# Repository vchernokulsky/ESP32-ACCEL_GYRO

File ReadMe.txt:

Структура проекта:

hardware - проект разработанного устройства для САПР KiCad

firmware - исходники прошивки для устройства (Micropython)

software - исходники приложения для сбора данных (Microsoft Visual Studio 2019 / C# WPF)

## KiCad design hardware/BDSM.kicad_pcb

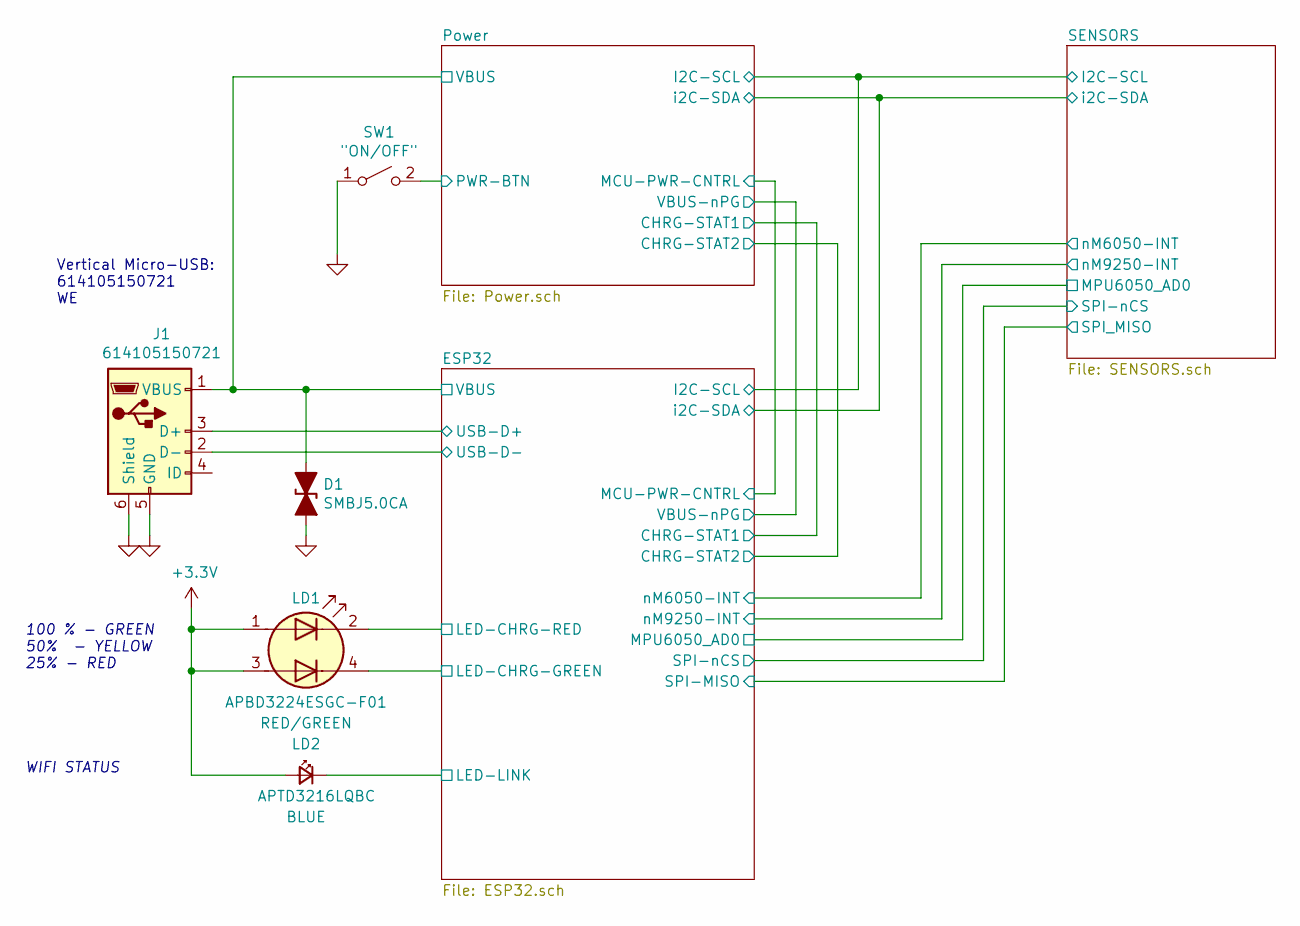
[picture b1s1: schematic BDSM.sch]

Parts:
D1: SMBJ5.0CA; D_SMB; PartNumber SMBJ5.0CA
J1: 614105150721; USB_Micro-B_Wuerth_614105150721_Vertical; PartNumber 614105150721
LD1: RED/GREEN; LED_Kingbright_APBD3224ESGC; PartNumber APBD3224ESGC-F01
LD2: BLUE; LED_1206_3216Metric_Pad1.42x1.75mm_HandSolder; PartNumber APTD3216LQBC
SW1: \"ON/OFF\"; Switch_Tactile_SMD_6x6mm; PartNumber 5-1437565-0

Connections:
+3V3: LD1.1 (A1), LD1.3 (A2), LD2.2 (A); also elsewhere on the board
/ESP32/LED-CHRG-GREEN: LD1.4 (K2); also elsewhere on the board
/ESP32/LED-CHRG-RED: LD1.2 (K1); also elsewhere on the board
/ESP32/LED-LINK: LD2.1 (K); also elsewhere on the board
/ESP32/USB-D+: J1.3 (D+); also elsewhere on the board
/ESP32/USB-D-: J1.2 (D-); also elsewhere on the board
/ESP32/VBUS: D1.1 (A1), J1.1 (VBUS); also elsewhere on the board
/Power/PWR-BTN: SW1.2 (B); also elsewhere on the board
GNDA: D1.2 (A2), J1.5 (GND), J1.6 (Shield), SW1.1 (A); also elsewhere on the board

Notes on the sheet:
Vertical Micro-USB: 614105150721 WE
100 % - GREEN 50% - YELLOW 25% - RED
WIFI STATUS

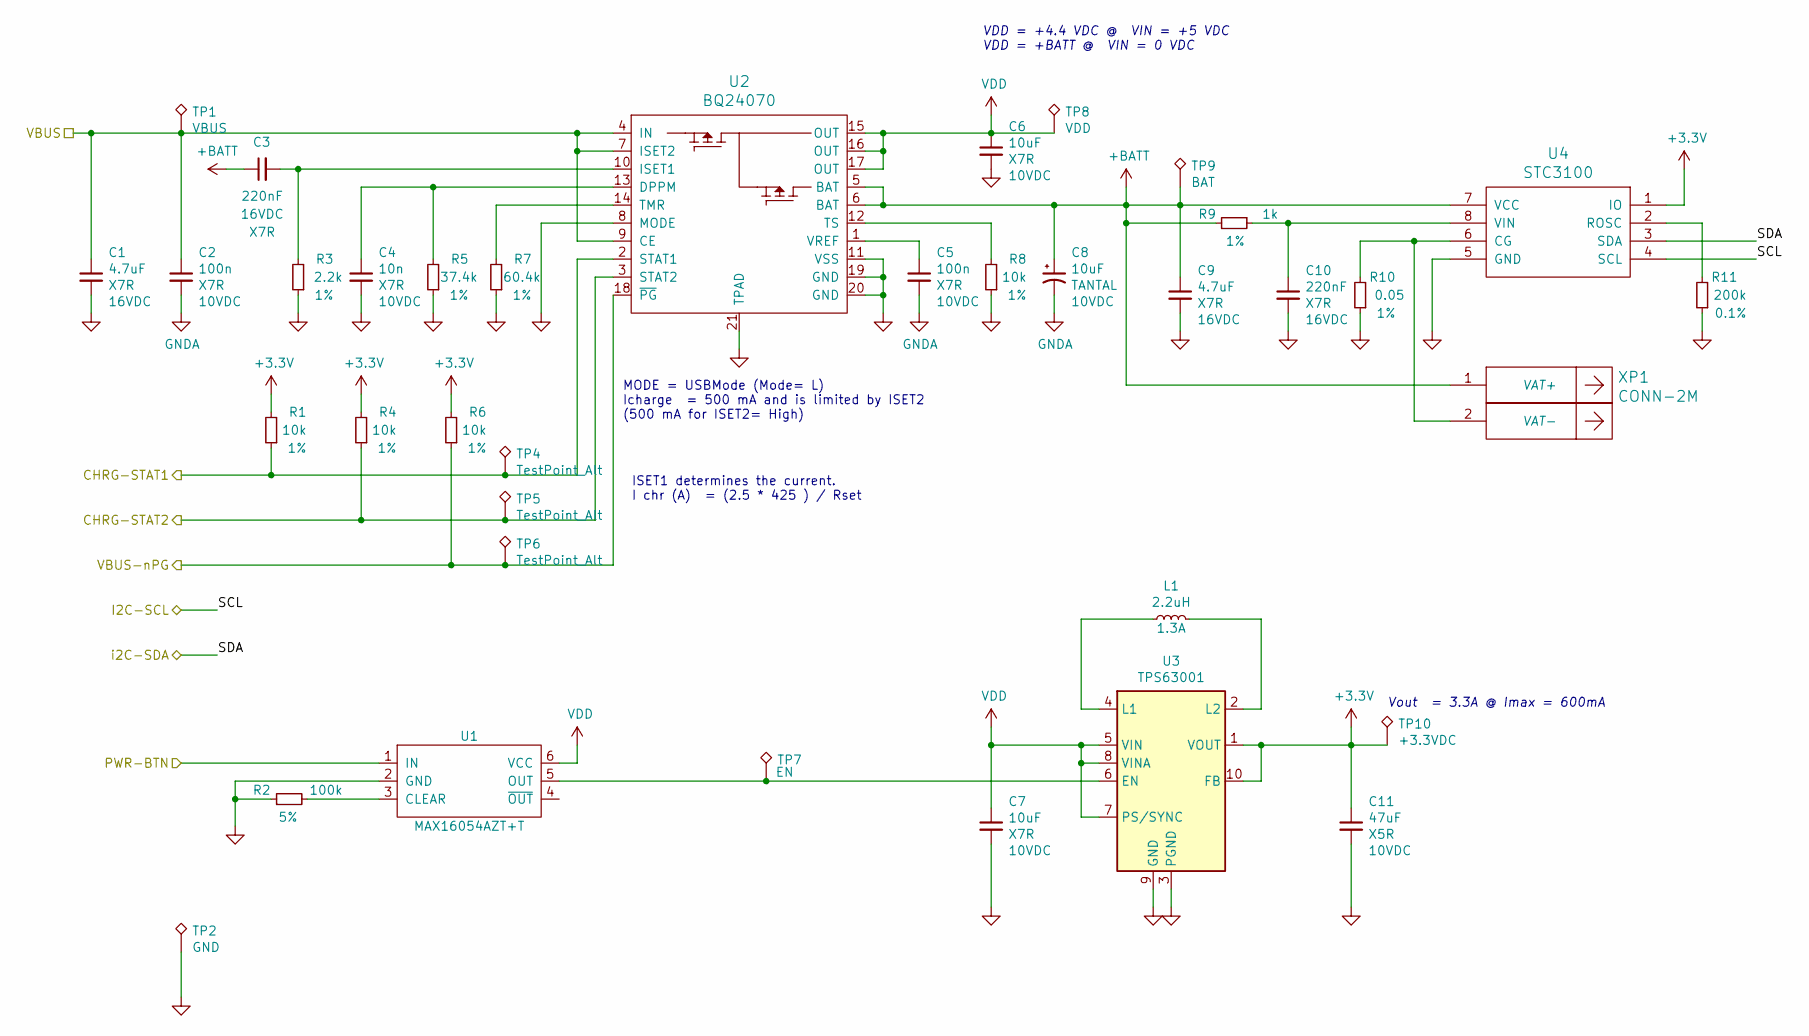
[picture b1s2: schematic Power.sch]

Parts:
C1, C9: 4.7uF; C_0805_2012Metric; Tolerance X7R; PartNumber CC0805KKX7R7BB105
C2, C5: 100n; C_0603_1608Metric; Tolerance X7R; PartNumber CC0603KRX7R9BB104
C3, C10: 220nF; C_0603_1608Metric; Tolerance X7R; PartNumber CC0603KRX7R7BB224
C4: 10n; C_0603_1608Metric; Tolerance X7R; PartNumber CC0603KRX7R9BB103
C6, C7: 10uF; C_0805_2012Metric; Tolerance X7R; PartNumber CL21B106KOQNNNE
C8: 10uF; CP_EIA-3528-21_Kemet-B; Tolerance TANTAL; PartNumber TAJB106K010RNJ
C11: 47uF; C_1206_3216Metric; Tolerance X5R; PartNumber C3216X5R1C476M160AB
L1: 2.2uH; L_1008_2520Metric; PartNumber LQM2HPN2R2MG0L
R1, R4, R6, R8: 10k; R_0603_1608Metric; Tolerance 1%; PartNumber RC0603FR-0710KL
R2: 100k; R_0603_1608Metric; Tolerance 5%; PartNumber RC0603JR-07100KL
R3: 2.2k; R_0603_1608Metric; Tolerance 1%; PartNumber RC0603FR-072K2L
R5: 37.4k; R_0603_1608Metric; Tolerance 1%; PartNumber RC0603FR-0737K4L
R7: 60.4k; R_0603_1608Metric; Tolerance 1%; PartNumber RC0603FR-0760K4L
R9: 1k; R_0603_1608Metric; Tolerance 1%; PartNumber CRCW06031K00FKEA
R10: 0.05; R_1206_3216Metric; Tolerance 1%; PartNumber RL1206FR-070R05L
R11: 200k; R_0603_1608Metric; Tolerance 0.1%; PartNumber RC0603FR-07200KL
TP1: VBUS; TestPoint_Pad_1.0x1.0mm; PartNumber PCB
TP2: GND; TestPoint_Keystone_5019_Minature; PartNumber PCB
TP4, TP5, TP6: TestPoint_Alt; TestPoint_Pad_1.0x1.0mm; PartNumber PCB
TP7: EN; TestPoint_Pad_1.0x1.0mm; PartNumber PCB
TP8: VDD; TestPoint_Pad_1.0x1.0mm; PartNumber PCB
TP9: BAT; TestPoint_Pad_1.0x1.0mm; PartNumber PCB
TP10: +3.3VDC; TestPoint_Pad_1.0x1.0mm; PartNumber PCB
U1: MAX16054AZT+T; SOT-23-6; PartNumber MAX16054AZT+T
U2: BQ24070; Texas_VQFN-RHL-20_ThermalVias; PartNumber BQ24070RHLR
U3: TPS63001; Texas_DRC0010J_ThermalVias; PartNumber TPS63001DRCT
U4: STC3100; MSOP-8_3x3mm_P0.65mm; PartNumber STC3100IST
XP1: CONN-2M; CWF-2R; PartNumber CWF-2R

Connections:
+3V3: C11.1, R1.2, R4.2, R6.2, TP10.1, U3.1 (VOUT), U3.10 (FB), U4.1 (IO); also elsewhere on the board
+BATT: C3.1, C8.1, C9.1, R9.2, TP9.1, U2.5 (BAT), U2.6 (BAT), U4.7 (VCC), XP1.1
/ESP32/CHRG-STAT1: R1.1, TP4.1, U2.2 (STAT1); also elsewhere on the board
/ESP32/CHRG-STAT2: R4.1, TP5.1, U2.3 (STAT2); also elsewhere on the board
/ESP32/I2C-SCL: U4.4 (SCL); also elsewhere on the board
/ESP32/VBUS: C1.1, C2.1, TP1.1, U2.4 (IN), U2.7 (ISET2), U2.9 (CE); also elsewhere on the board
/ESP32/VBUS-nPG: R6.1, TP6.1, U2.18 (~PG); also elsewhere on the board
/ESP32/i2C-SDA: U4.3 (SDA); also elsewhere on the board
/Power/PWR-BTN: U1.1 (IN); also elsewhere on the board
GNDA: C1.2, C2.2, C4.2, C5.2, C6.2, C7.2, C8.2, C9.2, C10.2, C11.2, R2.1, R3.1, R5.1, R7.1, R8.1, R10.1, R11.1, TP2.1, U1.2 (GND), U2.8 (MODE), U2.11 (VSS), U2.19 (GND), U2.20 (GND), U2.21 (TPAD), U3.3 (PGND), U3.9 (GND), U3.11 (PGND), U4.5 (GND); also elsewhere on the board
unnamed: C3.2, R3.2, U2.10 (ISET1)
unnamed: C4.1, R5.2, U2.13 (DPPM)
unnamed: C5.1, U2.1 (VREF)
unnamed: C10.1, R9.1, U4.8 (VIN)
unnamed: L1.1, U3.4 (L1)
unnamed: L1.2, U3.2 (L2)
unnamed: R2.2, U1.3 (CLEAR)
unnamed: R7.2, U2.14 (TMR)
unnamed: R8.2, U2.12 (TS)
unnamed: R10.2, U4.6 (CG), XP1.2
unnamed: R11.2, U4.2 (ROSC)
unnamed: TP7.1, U1.5 (OUT), U3.6 (EN)
VDD: C6.1, C7.1, TP8.1, U1.6 (VCC), U2.15 (OUT), U2.16 (OUT), U2.17 (OUT), U3.5 (VIN), U3.7 (PS/SYNC), U3.8 (VINA)

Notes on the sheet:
VDD = +4.4 VDC @ VIN = +5 VDC VDD = +BATT @ VIN = 0 VDC
ISET1 determines the current. I chr (A) = (2.5 * 425 ) / Rset
MODE = USBMode (Mode= L) Icharge = 500 mA and is limited by ISET2 (500 mA for ISET2= High)
Vout = 3.3A @ Imax = 600mA

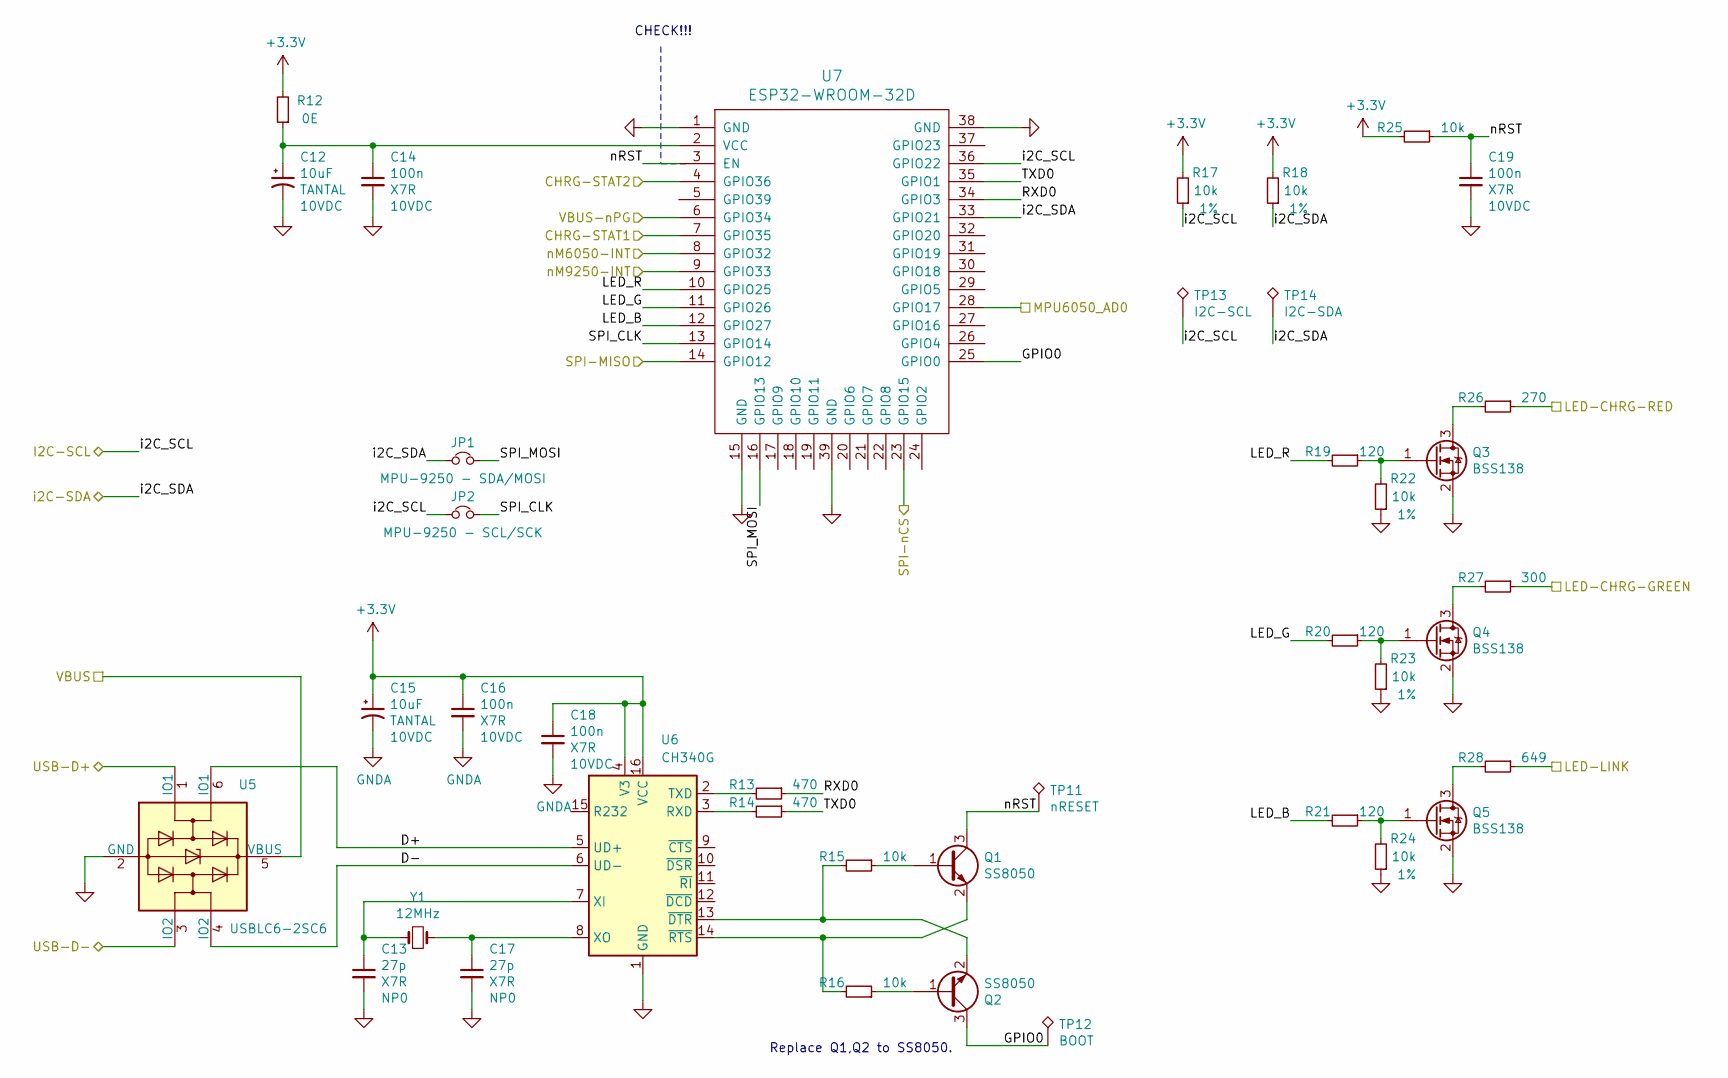
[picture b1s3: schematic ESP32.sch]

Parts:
C12, C15: 10uF; CP_EIA-3528-21_Kemet-B; Tolerance TANTAL; PartNumber TAJB106K010RNJ
C13, C17: 27p; C_0603_1608Metric; Tolerance X7R; PartNumber CC0603JRNPO9BN270
C14, C16, C18, C19: 100n; C_0603_1608Metric; Tolerance X7R; PartNumber CC0603KRX7R9BB104
JP1: MPU-9250 - SDA/MOSI; SolderJumper-2_P1.3mm_Open_TrianglePad1.0x1.5mm; PartNumber PCB
JP2: MPU-9250 - SCL/SCK; SolderJumper-2_P1.3mm_Open_TrianglePad1.0x1.5mm; PartNumber PCB
Q1, Q2: SS8050; SOT-23; PartNumber SS8050
Q3, Q4, Q5: BSS138; SOT-23; PartNumber BSS138LT1G
R12: 0E; R_0603_1608Metric; PartNumber RC0603FR-070RL
R13, R14: 470; R_0603_1608Metric; PartNumber RC0603FR-07470RL
R15, R16, R25: 10k; R_0603_1608Metric; PartNumber RC0603FR-0710KL
R17, R18, R22, R23, R24: 10k; R_0603_1608Metric; Tolerance 1%; PartNumber RC0603FR-0710KL
R19, R20, R21: 120; R_0603_1608Metric; PartNumber RC0603FR-07120RL
R26: 270; R_0603_1608Metric; PartNumber RC0603FR-07270RL
R27: 300; R_0603_1608Metric; PartNumber RC0603FR-07300RL
R28: 649; R_0603_1608Metric; PartNumber RC0603FR-07649RL
TP11: nRESET; TestPoint_Pad_1.0x1.0mm; PartNumber PCB
TP12: BOOT; TestPoint_Pad_1.0x1.0mm; PartNumber PCB
TP13: I2C-SCL; TestPoint_Pad_2.0x2.0mm; PartNumber PCB
TP14: I2C-SDA; TestPoint_Pad_2.0x2.0mm; PartNumber PCB
U5: USBLC6-2SC6; SOT-23-6; PartNumber USBLC6-2SC6
U6: CH340G; SOIC-16_3.9x9.9mm_P1.27mm; PartNumber CH340G
U7: ESP32-WROOM-32D; PartNumber ESP32-WROOM-32D
Y1: 12MHz; ABM3; PartNumber ABM3-12.000MHZ-D2Y-T

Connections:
+3V3: C15.1, C16.1, C18.1, R12.2, R17.2, R18.2, R25.2, U6.4 (V3), U6.16 (VCC); also elsewhere on the board
/ESP32/CHRG-STAT1: U7.7 (GPIO35); also elsewhere on the board
/ESP32/CHRG-STAT2: U7.4 (GPIO36); also elsewhere on the board
/ESP32/D+: U5.6 (IO1), U6.5 (UD+)
/ESP32/D-: U5.4 (IO2), U6.6 (UD-)
/ESP32/GPIO0: Q2.3 (C), TP12.1, U7.25 (GPIO0)
/ESP32/I2C-SCL: JP2.1, R17.1, TP13.1, U7.36 (GPIO22); also elsewhere on the board
/ESP32/LED-CHRG-GREEN: R27.1; also elsewhere on the board
/ESP32/LED-CHRG-RED: R26.1; also elsewhere on the board
/ESP32/LED-LINK: R28.1; also elsewhere on the board
/ESP32/LED_B: R21.2, U7.12 (GPIO27)
/ESP32/LED_G: R20.2, U7.11 (GPIO26)
/ESP32/LED_R: R19.2, U7.10 (GPIO25)
/ESP32/MPU6050_AD0: U7.28 (GPIO17); also elsewhere on the board
/ESP32/RXD0: R13.1, U7.34 (GPIO3)
/ESP32/SPI-MISO: U7.14 (GPIO12); also elsewhere on the board
/ESP32/SPI-nCS: U7.23 (GPIO15); also elsewhere on the board
/ESP32/SPI_CLK: JP2.2, U7.13 (GPIO14)
/ESP32/SPI_MOSI: JP1.2, U7.16 (GPIO13)
/ESP32/TXD0: R14.1, U7.35 (GPIO1)
/ESP32/USB-D+: U5.1 (IO1); also elsewhere on the board
/ESP32/USB-D-: U5.3 (IO2); also elsewhere on the board
/ESP32/VBUS: U5.5 (VBUS); also elsewhere on the board
/ESP32/VBUS-nPG: U7.6 (GPIO34); also elsewhere on the board
/ESP32/i2C-SDA: JP1.1, R18.1, TP14.1, U7.33 (GPIO21); also elsewhere on the board
/ESP32/nM6050-INT: U7.8 (GPIO32); also elsewhere on the board
/ESP32/nM9250-INT: U7.9 (GPIO33); also elsewhere on the board
/ESP32/nRST: C19.1, Q1.3 (C), R25.1, TP11.1, U7.3 (EN)
GNDA: C12.2, C13.2, C14.2, C15.2, C16.2, C17.2, C18.2, C19.2, Q3.2 (S), Q4.2 (S), Q5.2 (S), R22.1, R23.1, R24.1, U5.2 (GND), U6.1 (GND), U7.1 (GND), U7.15 (GND), U7.38 (GND), U7.39 (GND); also elsewhere on the board
unnamed: C12.1, C14.1, R12.1, U7.2 (VCC)
unnamed: C13.1, U6.7 (XI), Y1.1
unnamed: C17.1, U6.8 (XO), Y1.2
unnamed: Q1.1 (B), R15.1
unnamed: Q1.2 (E), R16.2, U6.14 (~RTS)
unnamed: Q2.1 (B), R16.1
unnamed: Q2.2 (E), R15.2, U6.13 (~DTR)
unnamed: Q3.1 (G), R19.1, R22.2
unnamed: Q3.3 (D), R26.2
unnamed: Q4.1 (G), R20.1, R23.2
unnamed: Q4.3 (D), R27.2
unnamed: Q5.1 (G), R21.1, R24.2
unnamed: Q5.3 (D), R28.2
unnamed: R13.2, U6.2 (TXD)
unnamed: R14.2, U6.3 (RXD)

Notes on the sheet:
CHECK!!!
Replace Q1,Q2 to SS8050.

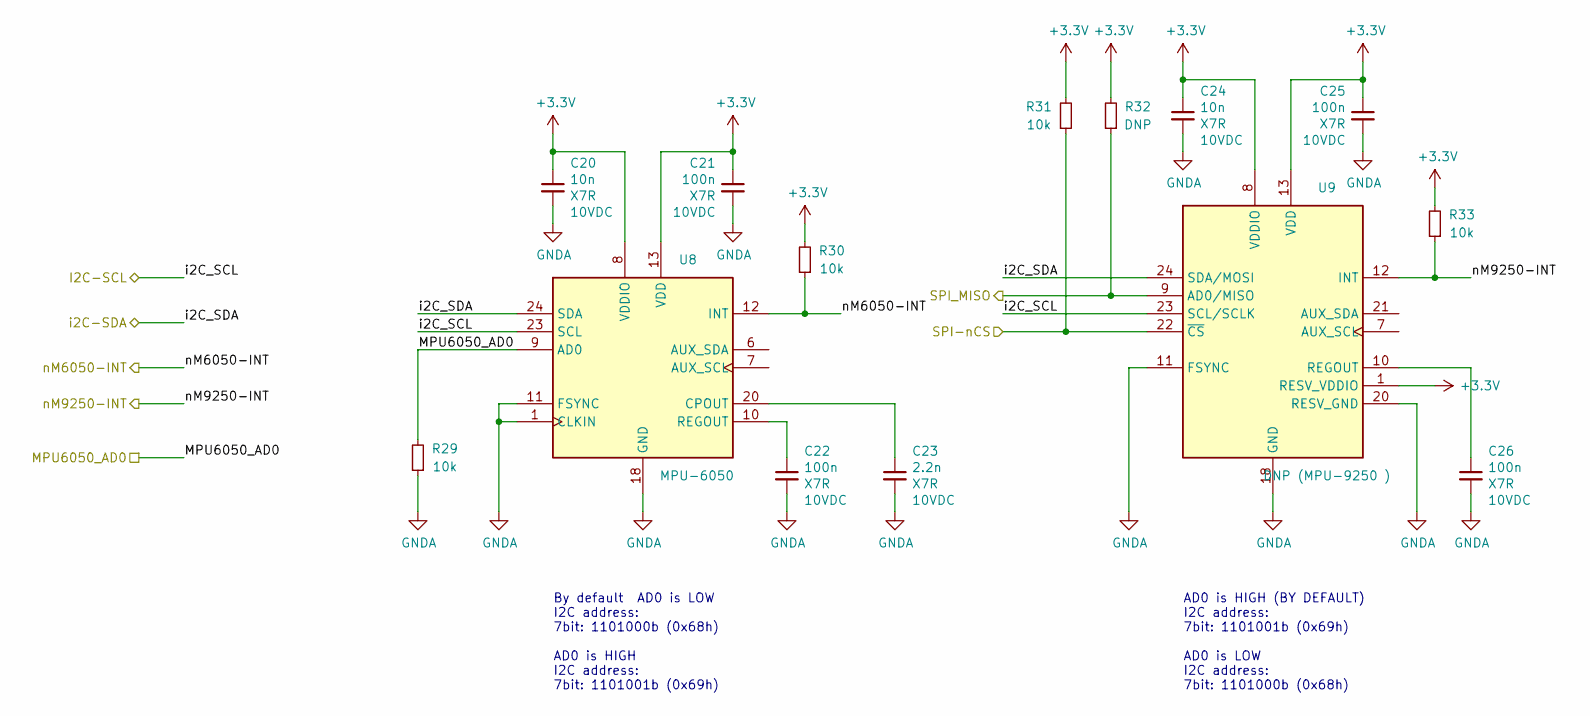
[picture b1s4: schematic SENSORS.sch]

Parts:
C20, C24: 10n; C_0603_1608Metric; Tolerance X7R; PartNumber CC0603KRX7R9BB103
C21, C22, C25, C26: 100n; C_0603_1608Metric; Tolerance X7R; PartNumber CC0603KRX7R9BB104
C23: 2.2n; C_0603_1608Metric; Tolerance X7R; PartNumber GRM188R71C222KA01D
R29, R30, R31, R33: 10k; R_0603_1608Metric; PartNumber RC0603FR-0710KL
R32: DNP; R_0603_1608Metric; PartNumber DNP
U8: MPU-6050; InvenSense_QFN-24_4x4mm_P0.5mm; PartNumber MPU-6050
U9: DNP (MPU-9250 ); InvenSense_QFN-24_3x3mm_P0.4mm; PartNumber DNP

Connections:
+3V3: C20.1, C21.1, C24.1, C25.1, R30.2, R31.2, R32.2, R33.2, U8.8 (VDDIO), U8.13 (VDD), U9.1 (RESV_VDDIO), U9.8 (VDDIO), U9.13 (VDD); also elsewhere on the board
/ESP32/I2C-SCL: U8.23 (SCL), U9.23 (SCL/SCLK); also elsewhere on the board
/ESP32/MPU6050_AD0: R29.2, U8.9 (AD0); also elsewhere on the board
/ESP32/SPI-MISO: R32.1, U9.9 (AD0/MISO); also elsewhere on the board
/ESP32/SPI-nCS: R31.1, U9.22 (~CS); also elsewhere on the board
/ESP32/i2C-SDA: U8.24 (SDA), U9.24 (SDA/MOSI); also elsewhere on the board
/ESP32/nM6050-INT: R30.1, U8.12 (INT); also elsewhere on the board
/ESP32/nM9250-INT: R33.1, U9.12 (INT); also elsewhere on the board
GNDA: C20.2, C21.2, C22.2, C23.2, C24.2, C25.2, C26.2, R29.1, U8.1 (CLKIN), U8.11 (FSYNC), U8.18 (GND), U9.11 (FSYNC), U9.18 (GND), U9.20 (RESV_GND); also elsewhere on the board
unnamed: C22.1, U8.10 (REGOUT)
unnamed: C23.1, U8.20 (CPOUT)
unnamed: C26.1, U9.10 (REGOUT)

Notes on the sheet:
By default AD0 is LOW I2C address: 7bit: 1101000b (0x68h) AD0 is HIGH I2C address: 7bit: 1101001b (0x69h)
AD0 is HIGH (BY DEFAULT) I2C address: 7bit: 1101001b (0x69h) AD0 is LOW I2C address: 7bit: 1101000b (0x68h)

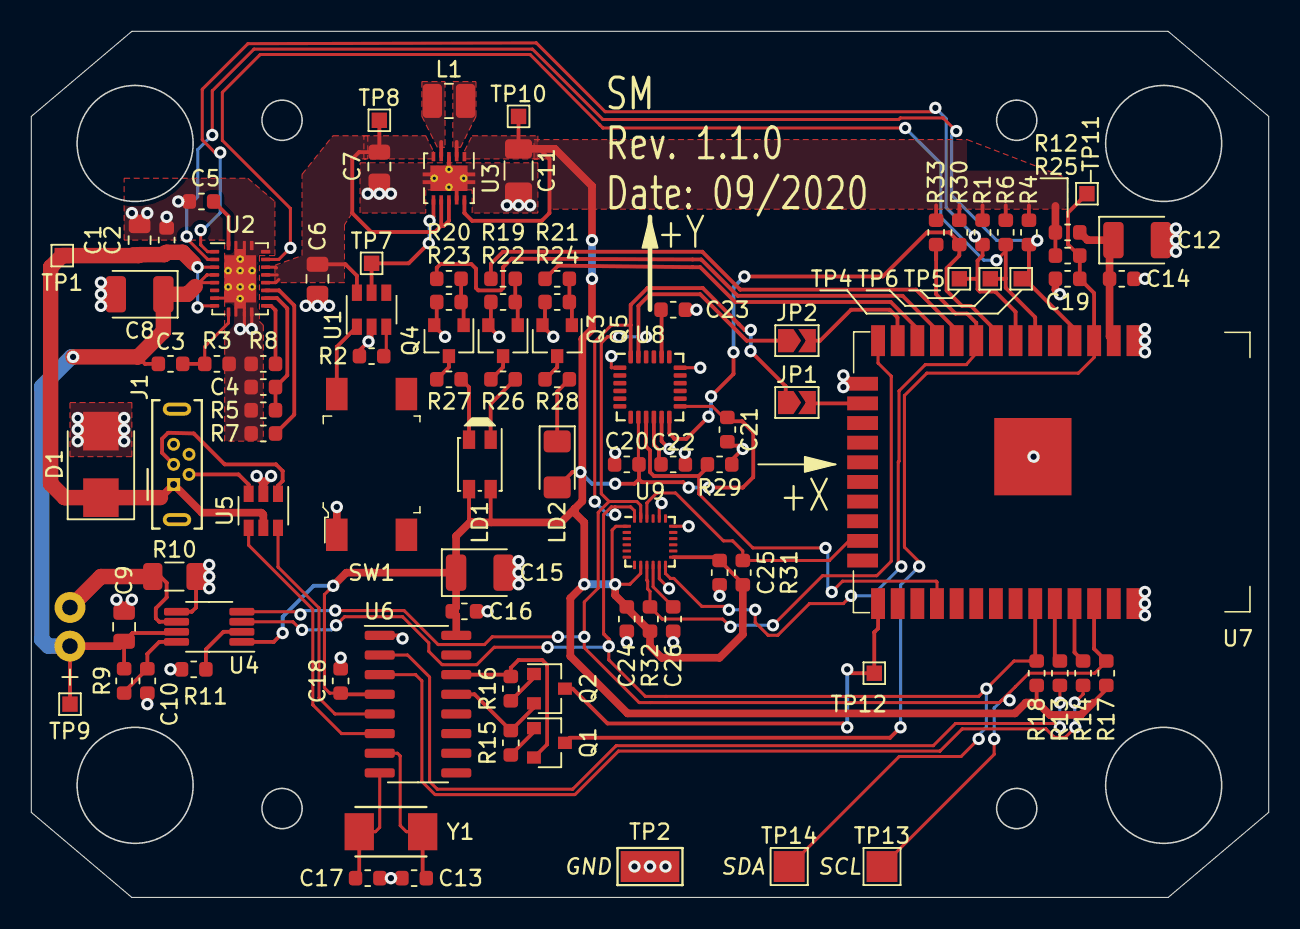
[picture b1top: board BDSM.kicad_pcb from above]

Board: 2 copper layers, 79.9 x 56.0 mm, 96 parts (1 on the bottom side), 62 nets.

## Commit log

2020-07-03 firmware add acceleration reading sending to socket
2020-07-03 reformate functions
2020-07-03 handle socket error
2020-07-03 add SocketServer port configuration from argv
2020-07-03 indicate socket connection by led blinkinh
2020-07-06 init AccelServer
2020-07-06 udp python example
2020-07-06 udp example for esp32
2020-07-06 udp broadcaster C# example
2020-07-07 broadcast server ip
2020-07-07 esp recv server ip
2020-07-07 esp send self info and get server port
2020-07-07 device info server sync
2020-07-07 add syncronization with devices
2020-07-08 change broadcasting port to 15000
2020-07-08 add device simulator
2020-07-08 sending data from esp
2020-07-08 c# receive data from esp with start-stop buttons
2020-07-08 fix receiving data from esp
2020-07-09 simple refactoring
2020-07-09 reform data_receiver usage for multiple devices
2020-07-09 devide received data on 18-bytes packages
2020-07-09 add time synchronization
2020-07-09 create class for MPU information
2020-07-10 add data sync
2020-07-10 fix acc gyro info converter
2020-07-14 Fix incorrect package sequence
2020-07-14 remove extra code
2020-07-14 Esp add mpu initializing
2020-07-14 fix AccelServer Lib
2020-07-14 add GtkGui for test
2020-07-14 convert acceleration to m/s^2
2020-07-14 convert gyro to deg/s
2020-07-15 get wifi ip address
2020-07-15 esp32 autostart
2020-07-15 make DeviceSyncronizer non static
2020-07-15 finish threads
2020-07-15 esp32 add calibration class
2020-07-15 calibrate values
2020-07-15 recalibrate mpu
2020-07-16 begin using MVVM
2020-07-17 mvvm show/hide no wifi conection lbl
2020-07-17 add buttons
2020-07-17 bind AccelServer and gui
2020-07-17 try to bind with device syncronizer
2020-07-20 get self ip
2020-07-20 show data receiving status
2020-07-20 chart example
2020-07-21 create point chart
2020-07-21 update chart
2020-07-22 change DataVisualisation toolkit on LiveChart
2020-07-23 1 Chart pagination 2 Chart view resampling 3 Change GUI layout
2020-07-23 GUI improvement
2020-07-24 auto start and restart ESP
2020-07-24 fix data visualization on start
2020-07-24 create view model for line seriea and chart
2020-07-24 create LabelVM
2020-07-24 create user control for Chart with buttons
2020-07-27 create Spinner
2020-07-27 add spinner for resampling
2020-07-27 create model and control for prev/next button
2020-07-27 show 6 charts
2020-07-28 add title on chart
2020-07-28 add try catch into main while
2020-07-28 put data into DB
2020-07-29 split gui on 2 progects: general part and specified for acceleration measurement part
2020-07-29 rename server project
2020-07-29 remove GtkGUI
2020-07-29 rename ImuServer namespace
2020-07-29 add Application type
2020-07-29 create project for angles measurement
2020-07-29 get SessionId on start from db
2020-07-29 add userName
2020-07-29 move sqlite database to root folder
2020-07-30 split DB for different app types
2020-07-30 Relocate files
2020-07-30 Project reconfigure
2020-07-31 Get IP-address from local interface
2020-07-31 Comments for some firmware functions
2020-08-03 fix exit
2020-08-03 esp32: send calibration info
2020-08-03 wpf: get calibration info
2020-08-03 update mainViewControl for angles measurement
2020-08-03 change label group name for app
2020-08-04 do not get data from extra devices in Angles measurement app
2020-08-04 add config file and led blinking on calibration
2020-08-04 remove extra sleep
2020-08-05 add led for charge state
2020-08-05 add show chart button
2020-08-05 Stub for use ethernet
2020-08-05 reset eror count
2020-08-05 fix time synchronization
2020-08-05 Fix incorrect database name
2020-09-04 Add ESP device schematic
2020-09-25 Add first hardware version
2020-09-25 ChargeMonitor - add charge state descriptions Config - revert default values main - simple refactoring
2020-09-25 Add gravity correction for device number 4
2020-09-25 ignores for hardware folder
2020-09-25 Fix ESP32 powering errors
2020-11-05 change ignores
2020-11-18 update gitignore
2020-11-18 update files for checking mpu data reading
2020-11-19 Create Device info table and put Device name and device status
2020-11-19 Add green status
2020-11-19 add device ip into table
2020-11-19 fix layout for angles measurement
2020-11-19 remove extra layouts
2020-11-19 show package received number
2020-11-24 move sessionId from accel server to SQLUtils
2020-11-25 setup led blinker for prepare stage
2020-11-25 blinking on data sending
2020-11-26 some rename
2020-11-26 update blinking, update exit from sending loop
2020-11-26 set up mvvm and speedup
2020-11-26 fix session id counter
2020-11-27 Update tools for for current socket commutnication order
2020-11-27 sd card example
2020-11-30 read battery parameters from stc3100
2020-11-30 move i2c reading to separate class
2020-11-30 get charge percent
2020-11-30 check is_charging on start
2020-12-01 Show SessionId
2020-12-01 show batery charge on device synchronized
2020-12-01 send battery charge on syncronization
2020-12-01 create start command
2020-12-01 create on stop command to device
2020-12-01 getting stop command
2020-12-02 update command receiving
2020-12-02 put commad andler socket into class
2020-12-02 handle ask state command
2020-12-02 fix senseresistor
2020-12-03 fix commandSocket
2020-12-03 Create command socket class
2020-12-03 SocketReconection looking for error
2020-12-08 DataReceiver change to state machine
2020-12-08 Fix BateryChargeConstants
2020-12-08 Fix synchronization
2020-12-08 set receiving thread name
2020-12-08 checking battery charge and device connection during wait_for_receive
2020-12-08 catch exception on receive
2020-12-08 create reconnection from every state, make actual device status
2020-12-09 Create thread for checking wifi connection
2020-12-09 correct thread finishing
2020-12-09 Flush socket buffer
2020-12-09 fix error: pushing start when reconnect
2020-12-09 finish fixing reconnection on start button pushong
2020-12-16 fix handling wrong battery charge values
2020-12-18 Update stc3100 setup and led charge indication
2020-12-29 Update reconection interval
2020-12-29 Check charge on start. Blink red if discharge
2021-03-31 some fix
2021-03-31 moving files to ubuntu
